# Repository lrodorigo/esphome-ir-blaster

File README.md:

# ESPHome IR-Blaster
## An high-power ultra-tiny IR Blaster

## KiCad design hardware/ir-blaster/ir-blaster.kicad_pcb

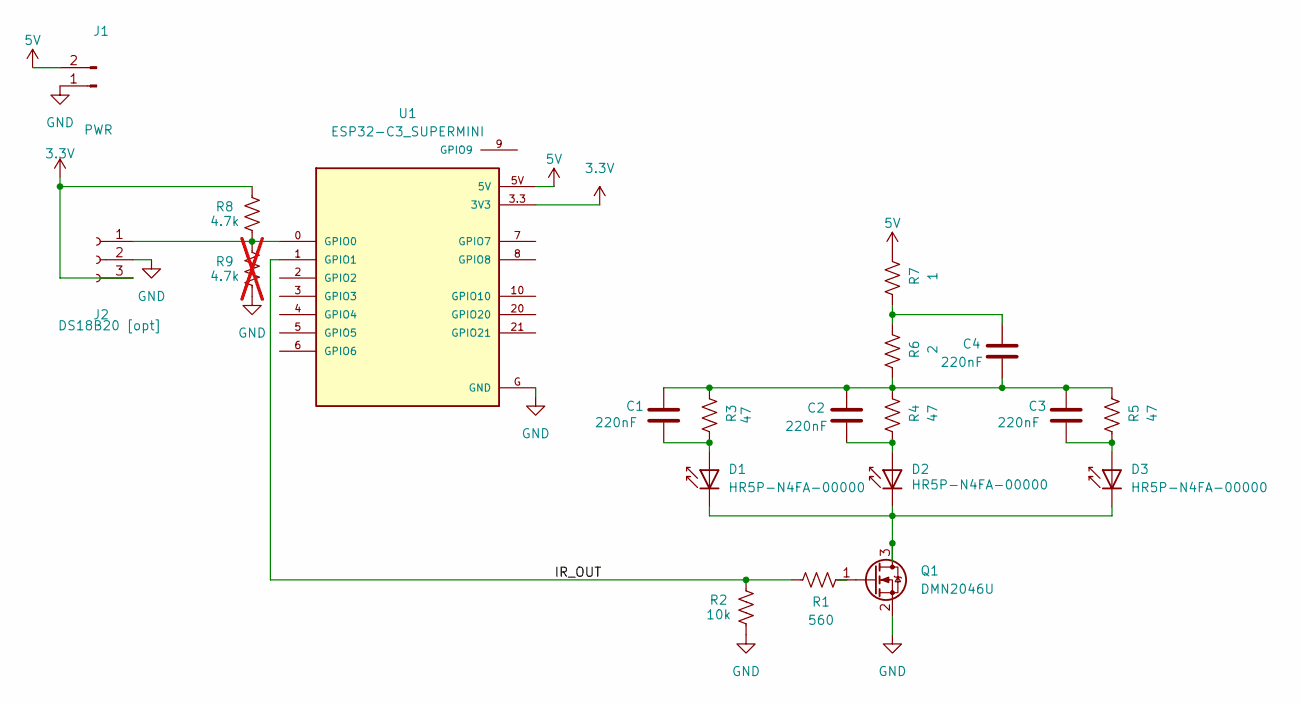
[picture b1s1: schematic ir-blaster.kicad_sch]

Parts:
C1, C2, C3, C4: 220nF; C_0805_2012Metric_Pad1.18x1.45mm_HandSolder
D1, D2, D3: HR5P-N4FA-00000; LED_D3.0mm_IRBlack
J1: PWR; PinHeader_1x02_P2.54mm_Vertical
J2: DS18B20 [opt]; PinHeader_1x03_P2.54mm_Vertical
Q1: DMN2046U; SOT-23
R1: 560; R_0805_2012Metric_Pad1.20x1.40mm_HandSolder
R2: 10k; R_0805_2012Metric_Pad1.20x1.40mm_HandSolder
R3, R4, R5: 47; R_0805_2012Metric_Pad1.20x1.40mm_HandSolder
R6: 2; R_0805_2012Metric_Pad1.20x1.40mm_HandSolder
R7: 1; R_0805_2012Metric_Pad1.20x1.40mm_HandSolder
R8: 4.7k; R_0805_2012Metric_Pad1.20x1.40mm_HandSolder
R9: 4.7k; R_0805_2012Metric_Pad1.20x1.40mm_HandSolder; not fitted
U1: ESP32-C3_SUPERMINI; MODULE_ESP32-C3_SUPERMINI

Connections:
3.3V: J2.3, R8.2, U1.3.3 (3V3)
5V: J1.2, R7.2, U1.5V
/IR_OUT: R1.1, R2.2, U1.1 (GPIO1)
GND: J1.1, J2.2, Q1.2 (S), R2.1, R9.1, U1.G (GND)
unnamed: C1.1, C2.1, C3.1, C4.2, R3.2, R4.2, R5.2, R6.1
unnamed: C4.1, R6.2, R7.1
unnamed: C1.2, D1.2 (A), R3.1
unnamed: D1.1 (K), D2.1 (K), D3.1 (K), Q1.3 (D)
unnamed: C2.2, D2.2 (A), R4.1
unnamed: C3.2, D3.2 (A), R5.1
unnamed: J2.1, R8.1, R9.2, U1.0 (GPIO0)
unnamed: Q1.1 (G), R1.2

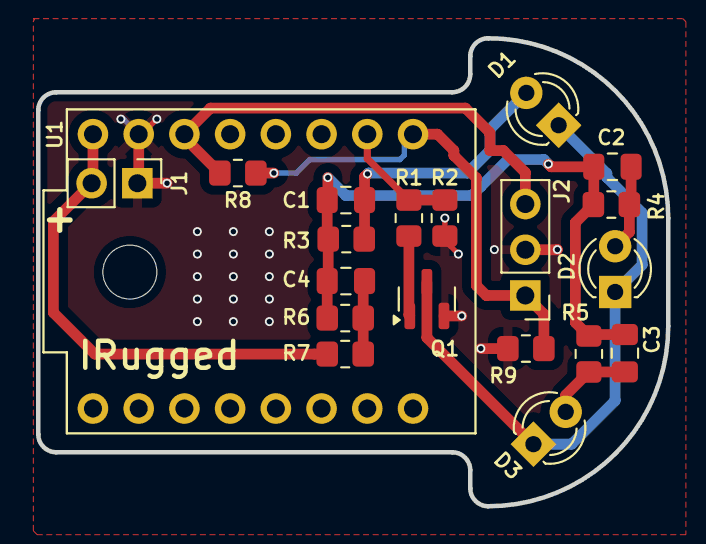
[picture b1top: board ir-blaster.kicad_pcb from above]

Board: 2 copper layers, 35.0 x 26.0 mm, 20 parts (0 on the bottom side), 12 nets.

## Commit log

2024-08-10 Gerber Export
2024-08-10 README and fix user
2024-08-11 added LTSpice sim
2024-08-15 New traces layout
2024-11-30 Python stub for radiator valves
2024-11-30 Esphome example
2024-12-04 Working version
2024-12-06 Working BLE Protocol
2024-12-06 Temperature readback
2024-12-07 TODO
2024-12-08 First quasi-working version
2024-12-08 Added RSSI monitoring
2024-12-08 Added RSSI reporting
2024-12-08 Requirements freezing
2024-12-08 Important Fix for multiple callbacks issue
2024-12-08 Doc-Strings
2024-12-08 Fix MQTT reconnection logic
2024-12-16 Fixes and ids
2024-12-19 Added more proxies
2025-01-01 Added ESPHome YAML for BT proxy
